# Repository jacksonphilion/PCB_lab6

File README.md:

Jackson Philion, Oct.3.2024, jphilion@g.hmc.edu

This repository contains the gerber and KiCad files to make a custom PCB for lab 6. Using the outline below, as well as the associated resources and references, I created the PCB to connect a DS1722 chip to a MikroBUS standard port. Our E155 protoboard has one such port. The DS1722 is a digital thermometer which communicates over the popular SPI interface. I elected to maintain the standard form factor of the MikroBUS standard, minus the notch, but chose to only include the silkscreen markings which I felt were most relevant. 

Activity Outline:     https://hmc-e155.github.io/lecture/pcb-activity/ \
Tutorials Referenced: https://www.youtube.com/playlist?list=PL3bNyZYHcRSUhUXUt51W6nKvxx2ORvUQB \
                      https://www.youtube.com/watch?v=3FGNw28xBr0 \
MikroBUS Standard:    https://download.mikroe.com/documents/standards/mikrobus/mikrobus-standard-specification-v200.pdf \
SOIC 8 Standard:      https://www.centralsemi.com/docs/PDD/SOIC-8PD.PDF \
DS1722 Datasheet:     https://www.analog.com/media/en/technical-documentation/data-sheets/DS1722.pdf \

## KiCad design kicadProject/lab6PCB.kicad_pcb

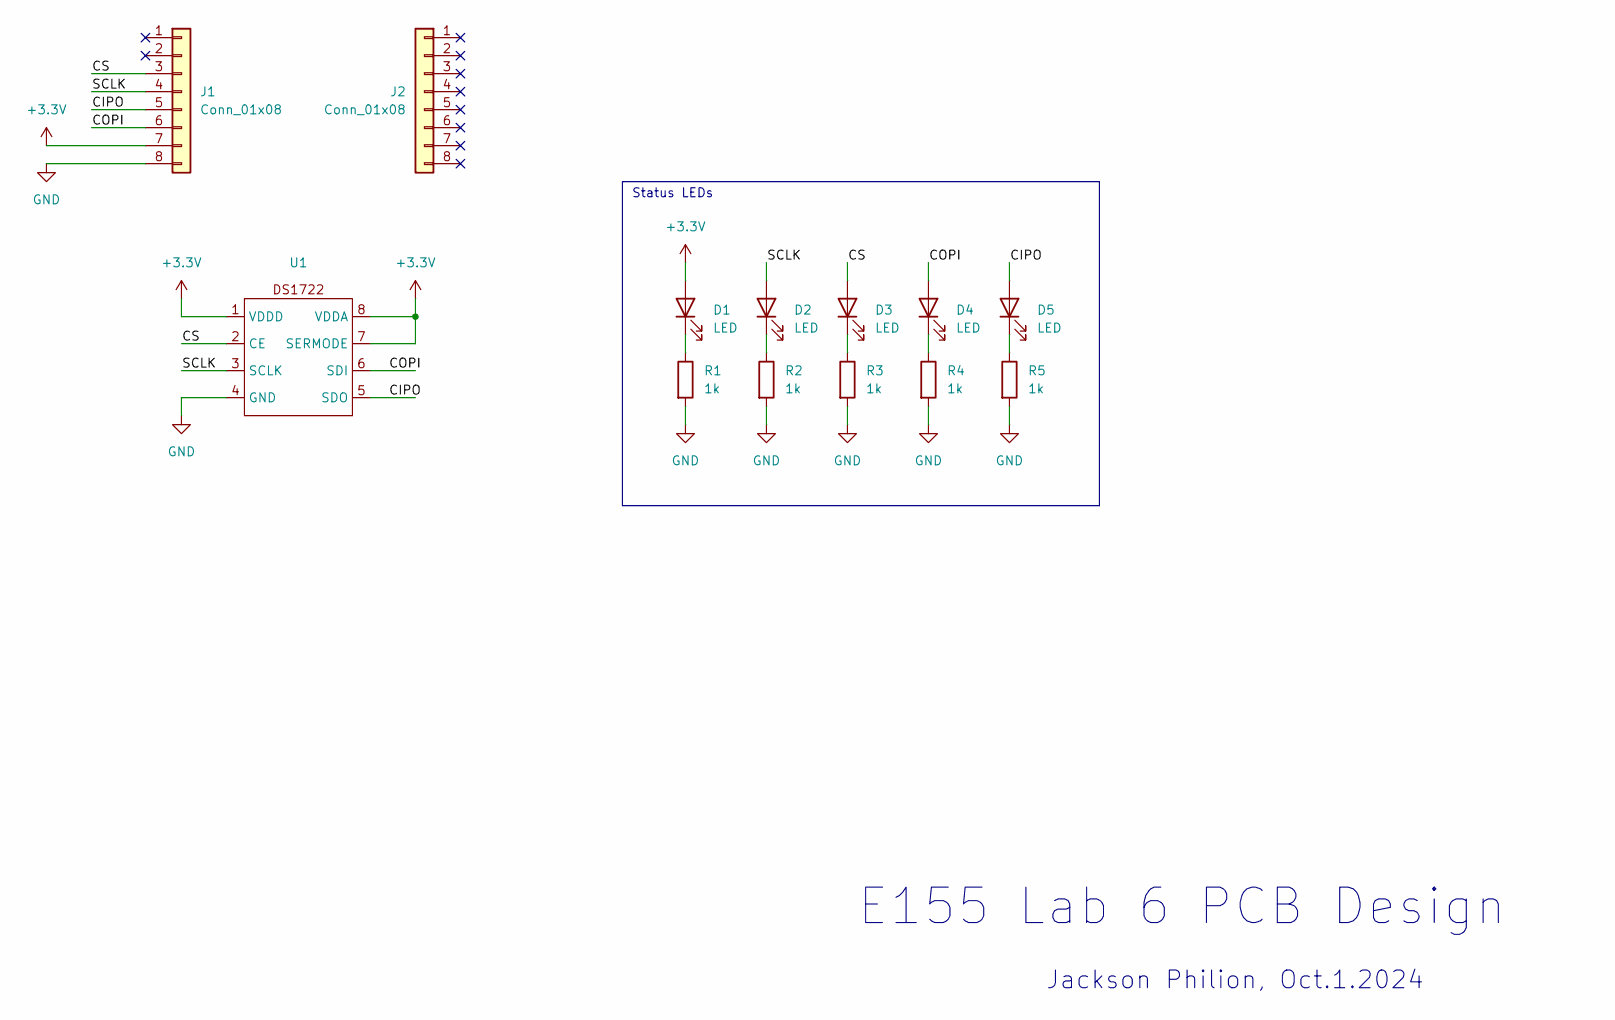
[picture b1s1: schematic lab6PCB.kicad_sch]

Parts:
D1, D2, D3, D4, D5: LED; LED_0805_2012Metric_Pad1.15x1.40mm_HandSolder
J1, J2: Conn_01x08; PinHeader_1x08_P2.54mm_Vertical
R1, R2, R3, R4, R5: 1k; R_0805_2012Metric_Pad1.20x1.40mm_HandSolder
U1: DS1722_SOIC_8_Custom

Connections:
+3.3V: D1.2 (A), J1.7, U1.1 (VDDD), U1.7 (SERMODE), U1.8 (VDDA)
/CIPO: D5.2 (A), J1.5, U1.5 (SDO)
/COPI: D4.2 (A), J1.6, U1.6 (SDI)
/CS: D3.2 (A), J1.3, U1.2 (CE)
/SCLK: D2.2 (A), J1.4, U1.3 (SCLK)
GND: J1.8, R1.2, R2.2, R3.2, R4.2, R5.2, U1.4 (GND)
unnamed: D1.1 (K), R1.1
unnamed: D2.1 (K), R2.1
unnamed: D3.1 (K), R3.1
unnamed: D4.1 (K), R4.1
unnamed: D5.1 (K), R5.1

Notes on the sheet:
Status LEDs
Jackson Philion, Oct.1.2024
E155 Lab 6 PCB Design

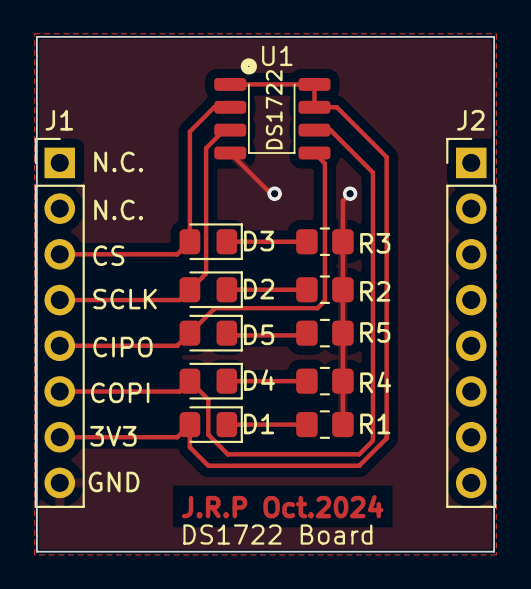
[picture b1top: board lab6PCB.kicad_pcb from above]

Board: 2 copper layers, 25.4 x 28.6 mm, 13 parts (0 on the bottom side), 11 nets.

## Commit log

2024-10-01 Initialize KiCad Blanks
2024-10-01 Finished Schematic
2024-10-01 Remove Backups
2024-10-04 Finished Gerber Files Organized

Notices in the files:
kicadProject/lab6PCB.kicad_pcb:
creativecommons.org/licenses/by/4.0
License: CC BY 4.0
